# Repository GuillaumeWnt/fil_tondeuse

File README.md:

View this project on [CADLAB.io](https://cadlab.io/project/30614).

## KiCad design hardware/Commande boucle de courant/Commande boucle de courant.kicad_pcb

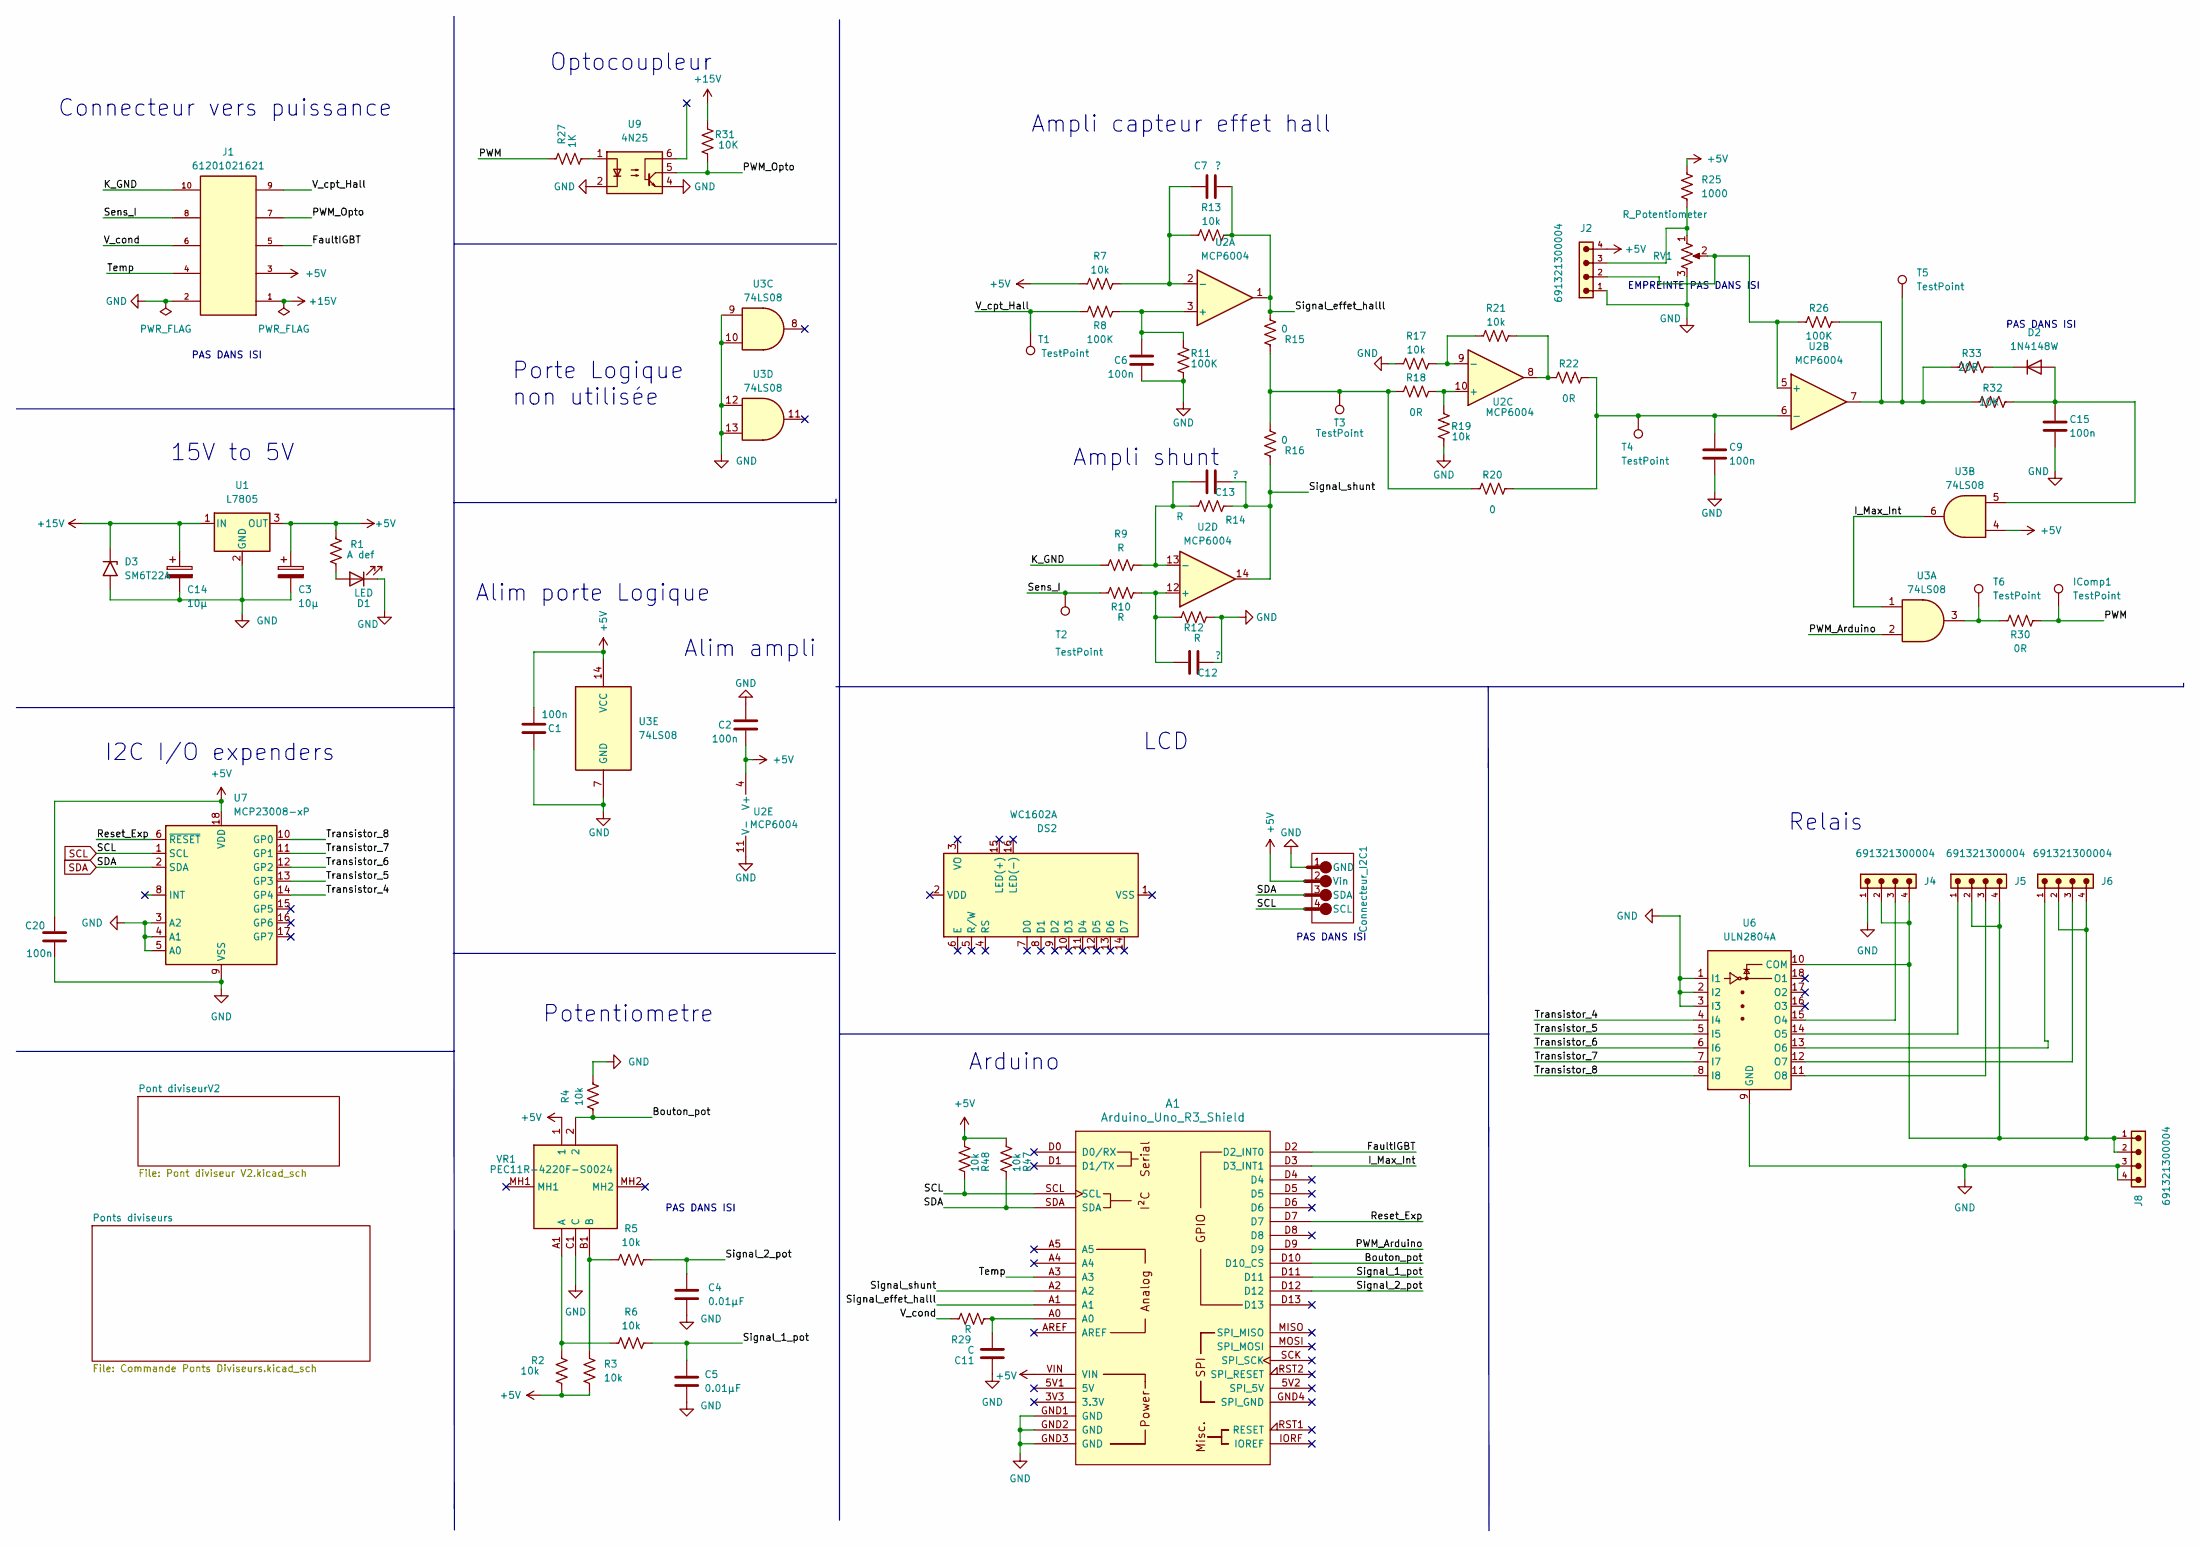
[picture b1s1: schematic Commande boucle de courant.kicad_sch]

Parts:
A1: Arduino_Uno_R3_Shield; Arduino_Uno_R3_Shield_LonPad
C1, C2, C6, C9, C15, C20: 100n; C_0805_2012Metric_Pad1.18x1.45mm_HandSolder
C3, C14: 10µ; C_1206_3216Metric
C4, C5: 0.01µF; C_1206_3216Metric
C7, C12, C13: ?; C_0805_2012Metric_Pad1.18x1.45mm_HandSolder
C11: C; C_1206_3216Metric
Connecteur_I2C1: Connecteur I2C
D1: LED; C_1206_3216Metric
D2: 1N4148W; D_SOD-123
D3: SM6T22A; D_SMB
DS2: WC1602A
IComp1: TestPoint; TestPoint_Keystone_5000-5004_Miniature
J1: 61201021621; Connecteur_10pins
J2, J4, J5, J6, J8: 691321300004; 691321100004; PART-NUMBER 691321100004
R1: A def; R_1206_3216Metric_Pad1.30x1.75mm_HandSolder
R2, R3, R4, R5, R6, R7, R13, R17, R19, R21, R47, R48: 10k; R_1206_3216Metric_Pad1.30x1.75mm_HandSolder
R8, R11, R26: 100K; R_1206_3216Metric_Pad1.30x1.75mm_HandSolder
R9, R10, R12, R14, R29: R; R_1206_3216Metric_Pad1.30x1.75mm_HandSolder
R15, R16, R20: 0; R_1206_3216Metric_Pad1.30x1.75mm_HandSolder
R18, R22, R30: 0R; R_1206_3216Metric_Pad1.30x1.75mm_HandSolder
R25: 1000; R_1206_3216Metric_Pad1.30x1.75mm_HandSolder
R27: 1K; R_1206_3216Metric_Pad1.30x1.75mm_HandSolder
R31, R32: 10K; R_1206_3216Metric_Pad1.30x1.75mm_HandSolder
R33: 20R; R_1206_3216Metric_Pad1.30x1.75mm_HandSolder
RV1: R_Potentiometer; Pot num TRIM_3296W-1-103LF
T1, T2, T3, T4, T5, T6: TestPoint; TestPoint_Keystone_5000-5004_Miniature
U1: L7805; TO-220-3_Vertical_Long
U2: MCP6004; TSSOP-14_4.4x5mm_P0.65mm
U3: 74LS08; SO_SOIC-14_3.9x8.7mm_P1.27mm
U6: ULN2804A; DIP-18_W7.62mm_LongPads
U7: MCP23008-xP; DIP-18_W7.62mm_LongPads
U9: 4N25; DIP-6_W7.62mm_LongPads
VR1: PEC11R-4220F-S0024; Potentiometre; Manufacturer_Part_Number PEC11R-4220F-S0024; Mouser Part Number 652-PEC11R-4220F-S24

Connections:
+5V: A1.VIN, C1.2, C2.2, C3.1, C20.2, Connecteur_I2C1.2 (Vin), J1.3, J2.4, R1.1, R2.2, R3.2, R7.2, R25.2, R47.1, R48.1, U1.3 (OUT), U2.4 (V+), U3.4, U3.14 (VCC), U7.18 (VDD), VR1.1; also elsewhere on the board
+15V: C14.1, D3.1 (A1), J1.1, R31.1, U1.1 (IN)
/Bouton_pot: A1.D10 (D10_CS), R4.2, VR1.2
/FaultIGBT: A1.D2 (D2_INT0), J1.5
/I_Max_Int: A1.D3 (D3_INT1), U3.1, U3.6
/K_GND: J1.10, R9.1
/PWM: IComp1.1, R27.1, R30.1
/PWM_Arduino: A1.D9, U3.2
/PWM_Opto: J1.7, R31.2, U9.5
/Reset_Exp: A1.D7, U7.6 (~RESET)
/Sens_I: J1.8, R10.1, T2.1
/Signal_1_pot: A1.D11, C5.1, R6.2
/Signal_2_pot: A1.D12, C4.2, R5.1
/Signal_effet_halll: A1.A1, C7.2, R13.1, R15.1, U2.1
/Signal_shunt: A1.A2, C13.2, R14.2, R16.2, U2.14
/Temp: A1.A3, J1.4
/Transistor_4: U6.4 (I4), U7.14 (GP4)
/Transistor_5: U6.5 (I5), U7.13 (GP3)
/Transistor_6: U6.6 (I6), U7.12 (GP2)
/Transistor_7: U6.7 (I7), U7.11 (GP1)
/Transistor_8: U6.8 (I8), U7.10 (GP0)
/V_cond: J1.6, R29.2
/V_cpt_Hall: J1.9, R8.2, T1.1
GND: A1.GND1 (GND), A1.GND2 (GND), A1.GND3 (GND), C1.1, C2.1, C3.2, C4.1, C5.2, C6.2, C9.2, C11.1, C12.2, C14.2, C15.2, C20.1, Connecteur_I2C1.1 (GND), D1.1 (K), D3.2 (A2), J1.2, J2.1, J4.1, J8.3, J8.4, R4.1, R11.2, R12.2, R17.2, R19.2, RV1.3, U1.2 (GND), U2.11 (V-), U3.7 (GND), U3.9, U3.10, U3.12, U3.13, U6.1 (I1), U6.2 (I2), U6.3 (I3), U6.9 (GND), U7.3 (A2), U7.4 (A1), U7.5 (A0), U7.9 (VSS), U9.2, U9.4, VR1.C1 (C); also elsewhere on the board
unnamed: A1.A0, C11.2, R29.1
unnamed: D1.2 (A), R1.2
unnamed: C15.1, D2.2 (A), R32.2, U3.5
unnamed: D2.1 (K), R33.2
unnamed: J2.3, R25.1, RV1.1
unnamed: R15.2, R16.1, R18.1, R20.1, T3.1
unnamed: R21.1, R22.1, U2.8
unnamed: R26.2, R32.1, R33.1, T5.1, U2.7
unnamed: R27.2, U9.1
unnamed: R30.2, T6.1, U3.3
unnamed: C6.1, R8.1, R11.1, U2.3 (+)
unnamed: C7.1, R7.1, R13.2, U2.2 (-)
unnamed: J2.2, R26.1, RV1.2, U2.5 (+)
unnamed: C9.1, R20.2, R22.2, T4.1, U2.6 (-)
unnamed: R18.2, R19.1, U2.10 (+)
unnamed: R17.1, R21.2, U2.9 (-)
unnamed: C12.1, R10.2, R12.1, U2.12 (+)
unnamed: C13.1, R9.2, R14.1, U2.13 (-)
unnamed: J4.2, J4.4, J5.2, J5.4, J6.2, J6.4, J8.1, J8.2, U6.10 (COM)
unnamed: J4.3, U6.15 (O4)
unnamed: J5.1, U6.14 (O5)
unnamed: J6.1, U6.13 (O6)
unnamed: J6.3, U6.12 (O7)
unnamed: J5.3, U6.11 (O8)
unnamed: R2.1, R6.1, VR1.A1 (A)
unnamed: R3.1, R5.2, VR1.B1 (B)
SCL: A1.SCL, Connecteur_I2C1.4 (SCL), R48.2, U7.1 (SCL); also elsewhere on the board
SDA: A1.SDA, Connecteur_I2C1.3 (SDA), R47.2, U7.2 (SDA); also elsewhere on the board

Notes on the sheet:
Relais
Porte Logique non utilisée
PAS DANS ISI
Ampli capteur effet hall
Optocoupleur
15V to 5V
I2C I/O expenders
Ampli shunt
Potentiometre
Alim ampli
EMPREINTE PAS DANS ISI
Connecteur vers puissance
LCD
Alim porte Logique
Arduino

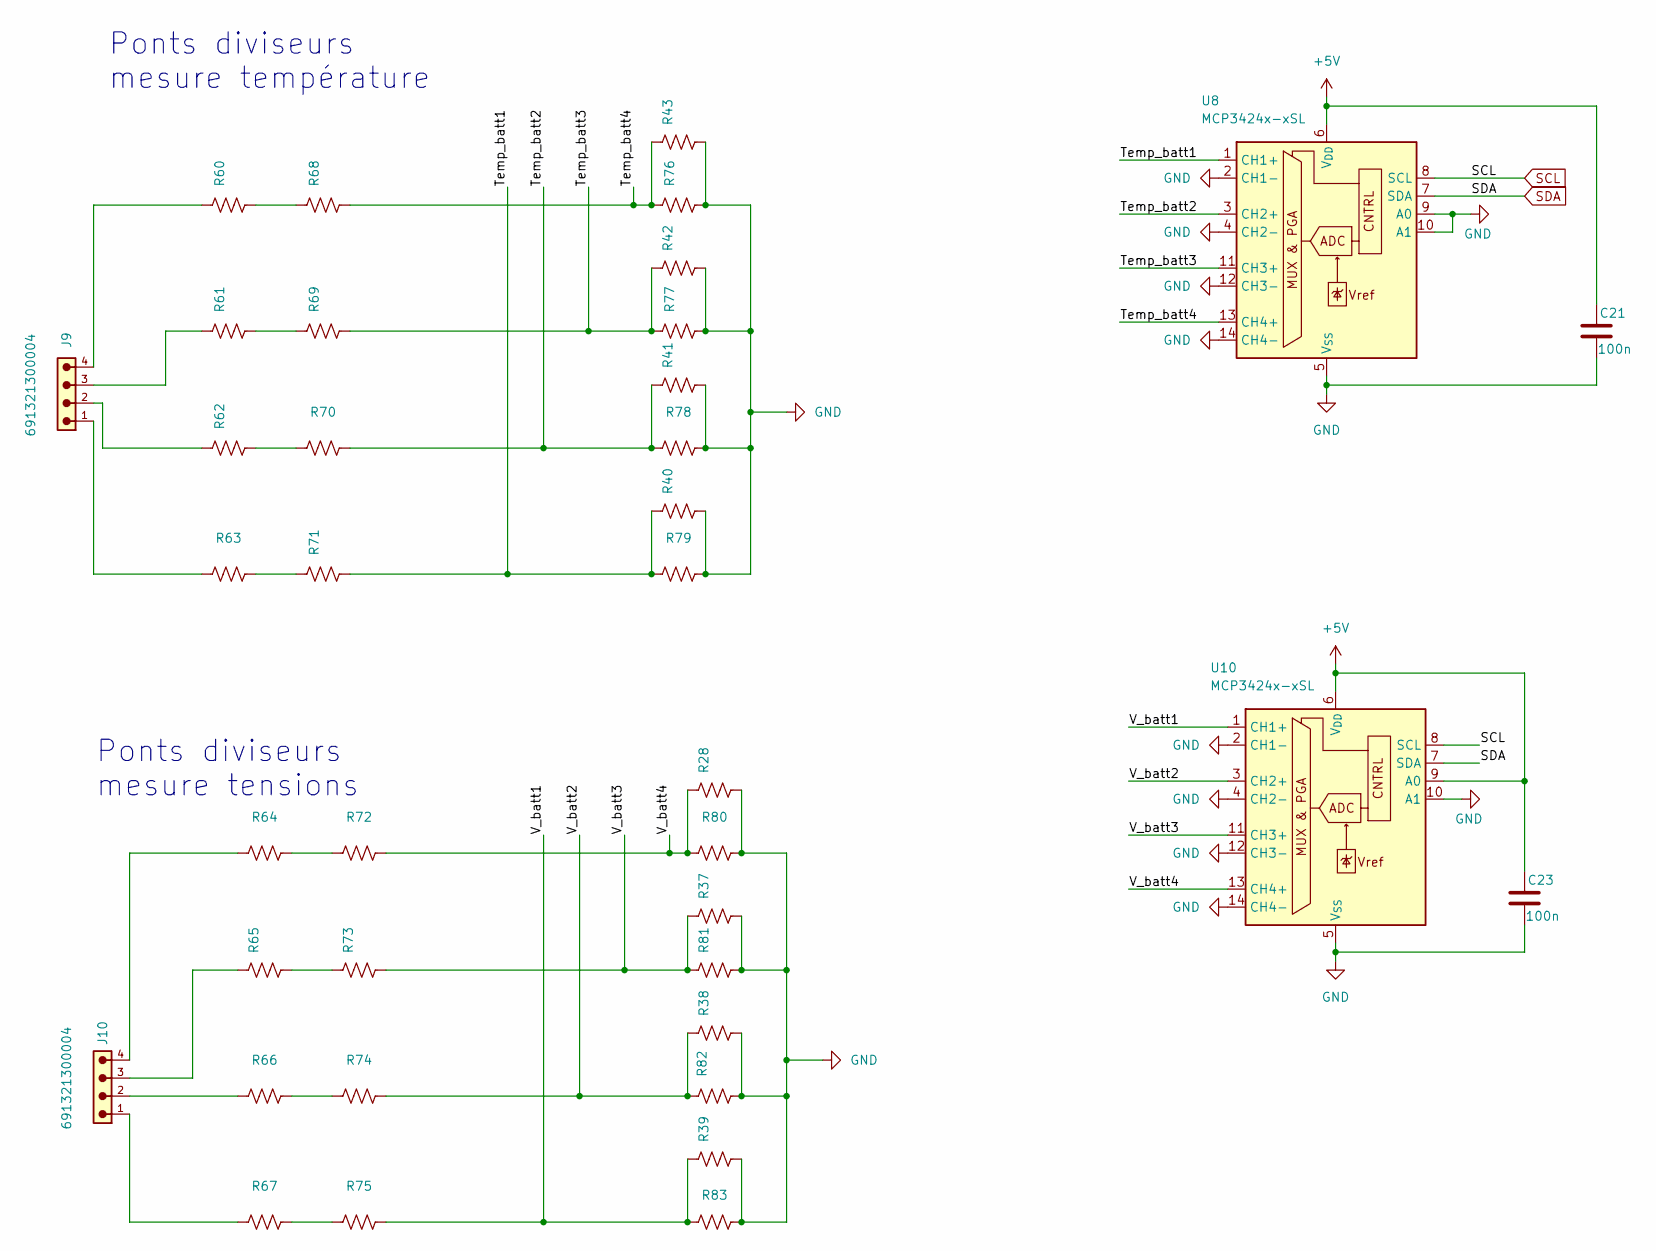
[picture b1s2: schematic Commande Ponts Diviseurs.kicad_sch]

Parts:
C21, C23: 100n; C_1206_3216Metric_Pad1.33x1.80mm_HandSolder
J9, J10: 691321300004; Connecteur_4pins; PART-NUMBER 691321300004
R28, R37, R38, R39, R40, R41, R42, R43, R60, R61, R62, R63, R64, R65, R66, R67, R68, R69, R70, R71, R72, R73, R74, R75, R76, R77, R78, R79, R80, R81, R82, R83: R_1206_3216Metric_Pad1.30x1.75mm_HandSolder
U8, U10: MCP3424x-xSL; SO_SOIC-14_3.9x8.7mm_P1.27mm

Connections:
+5V: C21.1, C23.1, U8.6 (V_{DD}), U10.6 (V_{DD}), U10.9 (A0); also elsewhere on the board
/Ponts diviseurs/Temp_batt1: R40.1, R71.2, R79.1, U8.1 (CH1+)
/Ponts diviseurs/Temp_batt2: R41.1, R70.2, R78.1, U8.3 (CH2+)
/Ponts diviseurs/Temp_batt3: R42.1, R69.2, R77.1, U8.11 (CH3+)
/Ponts diviseurs/Temp_batt4: R43.1, R68.2, R76.1, U8.13 (CH4+)
/Ponts diviseurs/V_batt1: R39.1, R75.2, R83.1, U10.1 (CH1+)
/Ponts diviseurs/V_batt2: R38.1, R74.2, R82.1, U10.3 (CH2+)
/Ponts diviseurs/V_batt3: R37.1, R73.2, R81.1, U10.11 (CH3+)
/Ponts diviseurs/V_batt4: R28.1, R72.2, R80.1, U10.13 (CH4+)
GND: C21.2, C23.2, R28.2, R37.2, R38.2, R39.2, R40.2, R41.2, R42.2, R43.2, R76.2, R77.2, R78.2, R79.2, R80.2, R81.2, R82.2, R83.2, U8.2 (CH1-), U8.4 (CH2-), U8.5 (V_{SS}), U8.9 (A0), U8.10 (A1), U8.12 (CH3-), U8.14 (CH4-), U10.2 (CH1-), U10.4 (CH2-), U10.5 (V_{SS}), U10.10 (A1), U10.12 (CH3-), U10.14 (CH4-); also elsewhere on the board
unnamed: J9.1, R63.1
unnamed: J9.2, R62.1
unnamed: J9.3, R61.1
unnamed: J9.4, R60.1
unnamed: J10.1, R67.1
unnamed: J10.2, R66.1
unnamed: J10.3, R65.1
unnamed: J10.4, R64.1
unnamed: R60.2, R68.1
unnamed: R61.2, R69.1
unnamed: R62.2, R70.1
unnamed: R63.2, R71.1
unnamed: R64.2, R72.1
unnamed: R65.2, R73.1
unnamed: R66.2, R74.1
unnamed: R67.2, R75.1
SCL: U8.8 (SCL), U10.8 (SCL); also elsewhere on the board
SDA: U8.7 (SDA), U10.7 (SDA); also elsewhere on the board

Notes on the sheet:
Ponts diviseurs mesure température
Ponts diviseurs mesure tensions

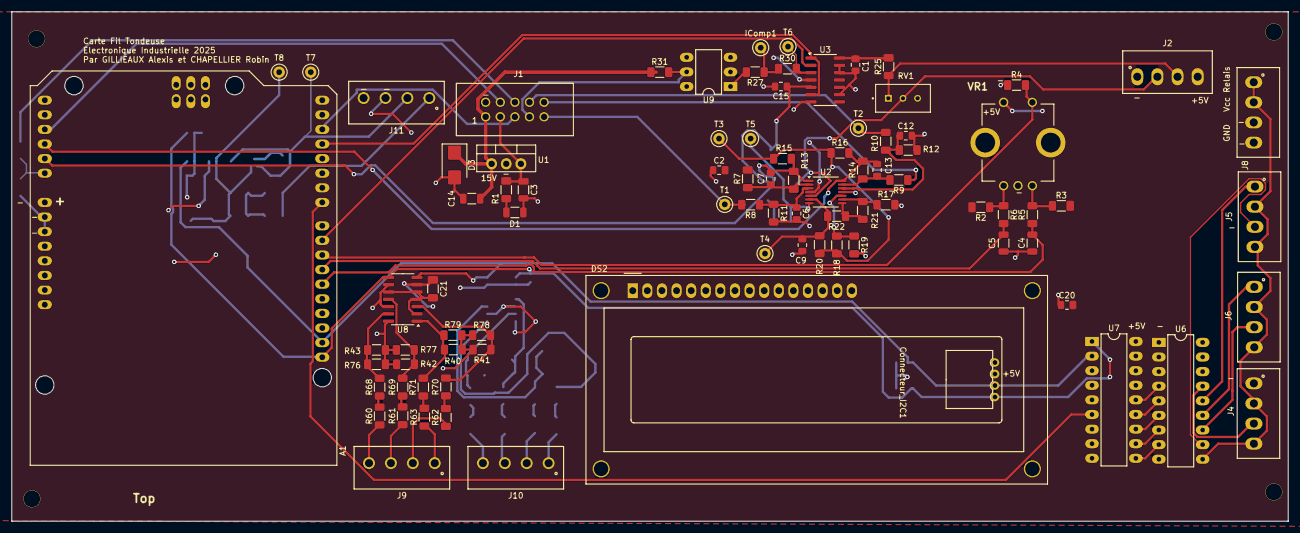
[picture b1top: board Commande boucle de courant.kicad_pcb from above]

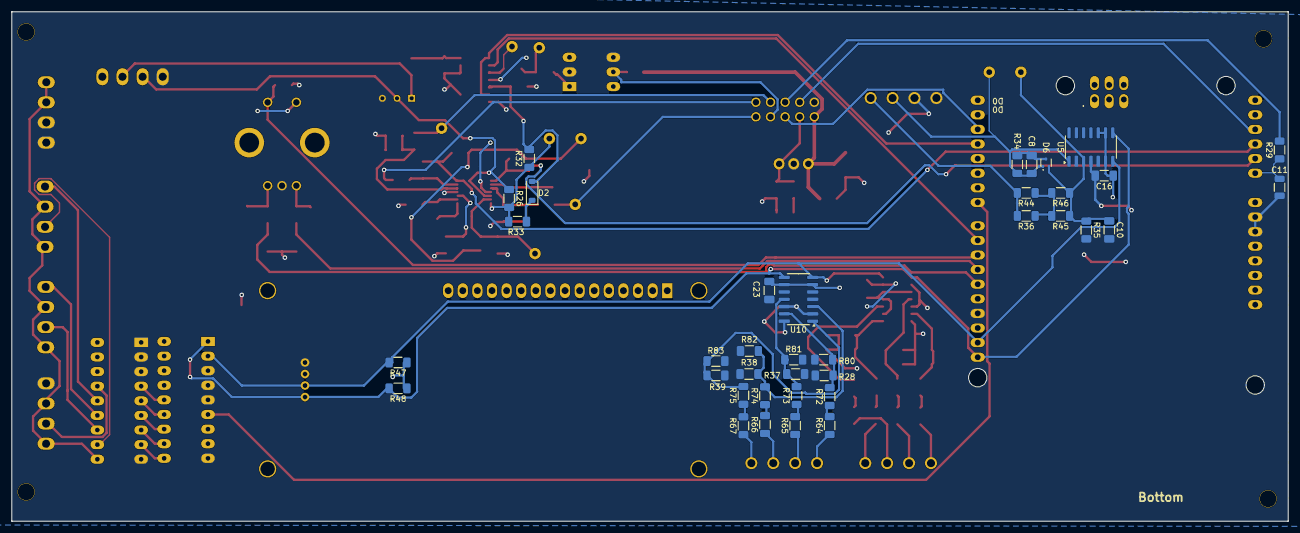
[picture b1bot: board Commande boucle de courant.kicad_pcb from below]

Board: 2 copper layers, 222.0 x 88.6 mm, 129 parts (38 on the bottom side), 80 nets.

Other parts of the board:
C8, C10: 10µ; C_1206_3216Metric_Pad1.33x1.80mm_HandSolder
C16: 100n; C_1206_3216Metric_Pad1.33x1.80mm_HandSolder
D6: RCLAMP0582BQTCT; SOT-523
H1, H2, H3, H4: MountingHole_Pad; MountingHole_3mm
J11: 691321100004; Connecteur_4pins
R34: 243; R_1206_3216Metric_Pad1.30x1.75mm_HandSolder
R35, R45, R46: 1K; R_1206_3216Metric_Pad1.30x1.75mm_HandSolder
R36, R44: 27K; R_1206_3216Metric_Pad1.30x1.75mm_HandSolder
T7, T8: TestPoint; TestPoint_Keystone_5000-5004_Miniature
U5: MCP3424x-xSL; SO_SOIC-14_3.9x8.7mm_P1.27mm

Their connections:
+5V: C16.1, U5.6 (V_{DD}), U5.9 (A0), U5.10 (A1); also elsewhere on the board
/Pont diviseurV2/Temp_batt1: C8.1, D6.1 (K1), J11.2, R34.1, T7.1, U5.1 (CH1+)
/Pont diviseurV2/Tension_batt1: C10.1, D6.2 (K2), R35.1, R45.1, R46.1, T8.1, U5.3 (CH2+)
GND: C8.2, C10.2, C16.2, D6.3 (A), J11.3, J11.4, R34.2, R35.2, U5.2 (CH1-), U5.4 (CH2-), U5.5 (V_{SS}); also elsewhere on the board
unnamed: J11.1, R36.2, R44.2
unnamed: R36.1, R44.1, R45.2, R46.2
SCL: U5.8 (SCL); also elsewhere on the board
SDA: U5.7 (SDA); also elsewhere on the board

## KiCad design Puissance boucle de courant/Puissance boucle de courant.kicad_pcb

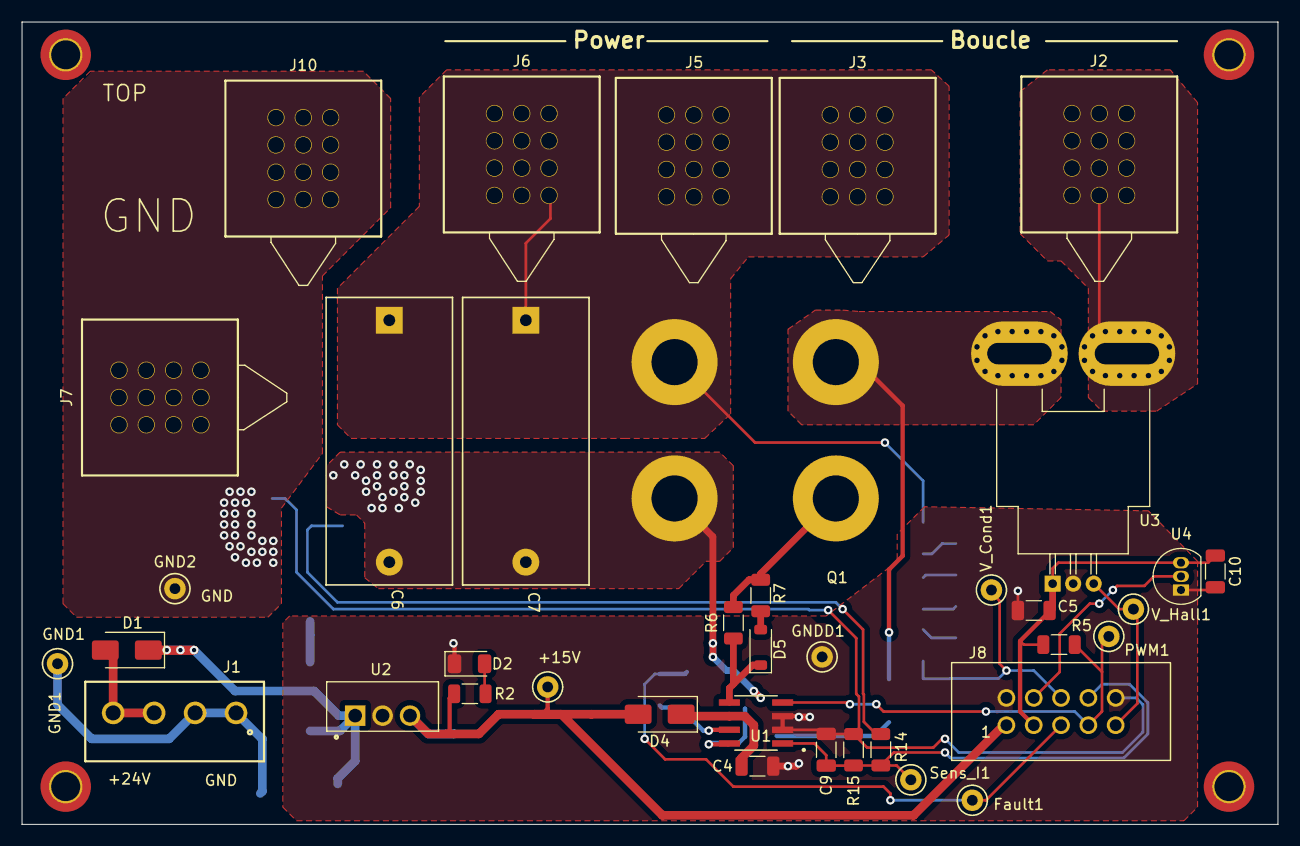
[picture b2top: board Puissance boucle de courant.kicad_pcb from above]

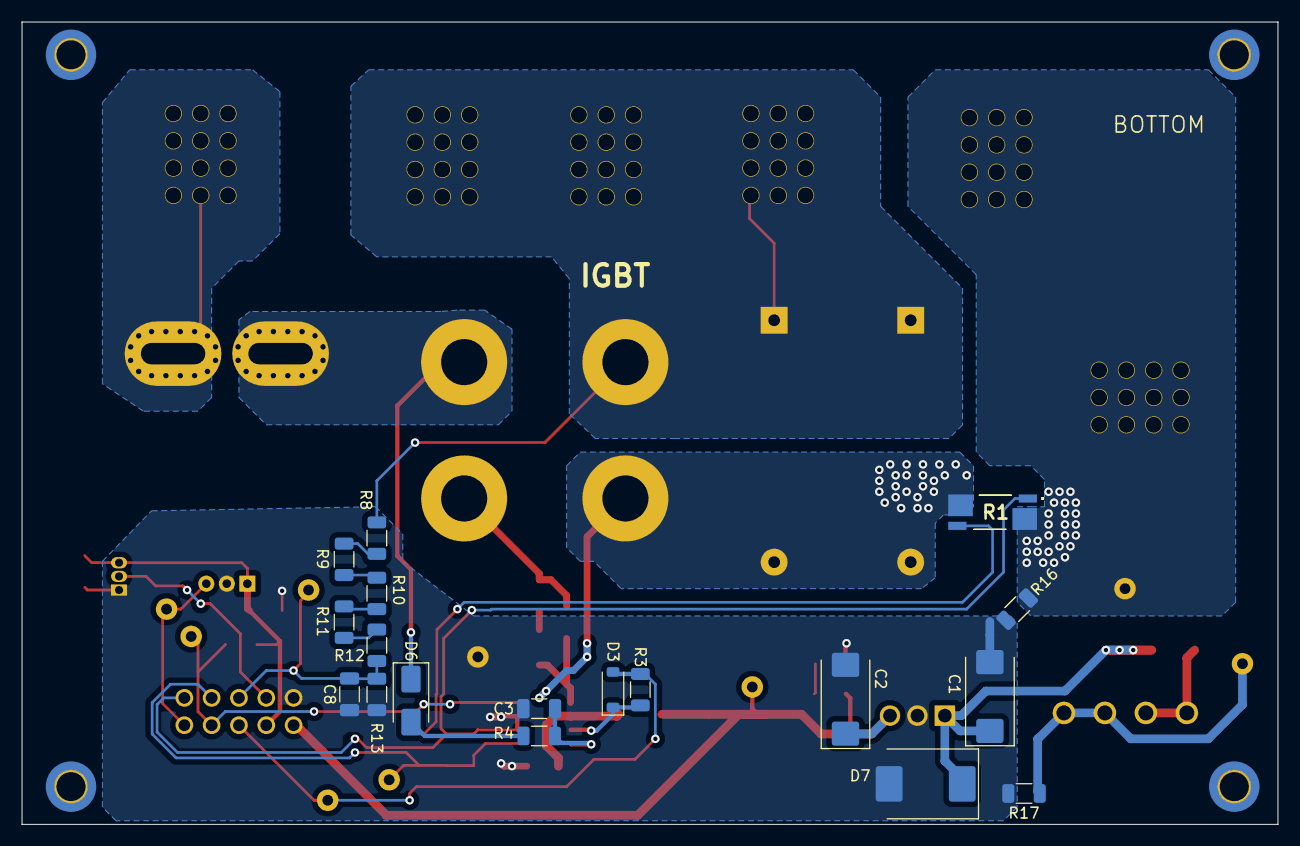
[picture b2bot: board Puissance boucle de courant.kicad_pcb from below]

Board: 2 copper layers, 116.8 x 74.6 mm, 60 parts (18 on the bottom side), 30 nets.

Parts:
C1, C2: 10µF; CP_EIA-7343-30_AVX-N_Pad2.25x2.55mm_HandSolder
C3, C4: 10µF; C_1206_3216Metric
C5, C8, C9, C10: 100nF; C_1206_3216Metric
C6, C7: 1µF; CAP_890334026027_WRE
D1, D4, D6: NRVA4007T3G; D_SMA
D2: LED; LED_1206_3216Metric
D3, D5: D_SOD-123
D7: B320; D_SMC
Fault1: TestPoint; TestPoint_Keystone_5000-5004_Miniature
GND1, GND2: TestPoint; TestPoint_Keystone_5000-5004_Miniature
GNDD1: TestPoint; TestPoint_Keystone_5000-5004_Miniature
H1, H2, H3, H4: MountingHole; MountingHole_2.7mm_M2.5_DIN965_Pad_TopBottom
J1: 691321300004
J2, J3, J5, J6, J7, J10: Conn_01x01_Socket; WP-PLUG_7464000
J8: 61201021621
PWM1: TestPoint; TestPoint_Keystone_5000-5004_Miniature
Q1: APT75GT120JU2; GENESIC_MBR200100CTS bis
R1: 0,002R; WSK25122L000FEA
R2, R3, R4, R6, R7, R14, R15: R; R_1206_3216Metric
R5, R13: 5k; R_1206_3216Metric
R8, R9, R10, R11: 50k; R_1206_3216Metric
R12: 11k; R_1206_3216Metric
R16, R17: 0R; R_1206_3216Metric
Sens_I1: TestPoint; TestPoint_Keystone_5000-5004_Miniature
TP3: TestPoint; TestPoint_Keystone_5000-5004_Miniature
U1: MC33153DG; SOIC127P600X265-8N
U2: L7815; TO255P1040X460X1935-3
U3: ACS770xCB-050U-PFF; Allegro_CB_PFF
U4: DS18B20; TO-92_Inline
V_Cond1: TestPoint; TestPoint_Keystone_5000-5004_Miniature
V_Hall1: TestPoint; TestPoint_Keystone_5000-5004_Miniature

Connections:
+5V: C5.1, C10.1, J8.3, R5.1, U3.1 (VCC), U4.3 (V_{DD})
+15V: C2.1, D4.2 (A), J8.1, R2.1, TP3.1, U2.3 (OUT)
+24V: C1.1, D1.1 (K), D7.1 (K), U2.1 (IN)
/+Boucle: C6.1, C7.1, J3.1, J5.1, J6.1, Q1.3 (K), R8.1
/-Boucle: J2.1, U3.4 (IP+)
/Driver_out: D5.1 (K), R6.1, U1.5 (DRIVE_OUT)
/FaultIGBT: D3.2 (A), Fault1.1, J8.5, R3.1
/PWM_Arduino: J8.7, PWM1.1, R5.2, U1.4 (~INPUT)
/Sens_I: C9.1, J8.8, R14.2, R15.1, Sens_I1.1, U1.1 (CURRENT_SEN_IN)
/Temp: J8.4, U4.2 (DQ)
/V_cond: C8.2, J8.6, R12.2, R13.1, V_Cond1.1
/V_cpt_Hall: J8.9, U3.3 (VIOUT), V_Hall1.1
/Vout_IGBT: C6.2, C7.2, Q1.1 (E), R1.I2
/Vout_cpt: D6.1 (K), Q1.4 (C), U3.5 (IP-)
GND: GND2.1, J7.1, J10.1, R1.I1, R16.2
GND1: GND1.1, J1.1, J1.2, R17.1
GNDD: C1.2, C2.2, C3.2, C4.2, C5.2, C8.1, C9.2, C10.2, D2.1 (K), D7.2 (A), GNDD1.1, J8.2, J8.10, R1.E1, R13.2, R15.2, R16.1, R17.2, U1.2 (KELVIN_GND), U1.3 (VEE), U2.2 (GND), U3.2 (GND), U4.1 (GND)
unnamed: D1.2 (A), J1.3, J1.4
unnamed: D2.2 (A), R2.2
unnamed: D3.1 (K), R3.2, U1.7 (FAULT_OUT)
unnamed: C4.1, D4.1 (K), U1.6 (VCC)
unnamed: D5.2 (A), R7.1
unnamed: D6.2 (A), R4.1
unnamed: Q1.2 (G), R6.2, R7.2
unnamed: R1.E2, R14.1
unnamed: R8.2, R9.1
unnamed: R9.2, R10.1
unnamed: R10.2, R11.1
unnamed: R11.2, R12.1
unnamed: C3.1, R4.2, U1.8 (FAULT_BLANKING/DESATURATION_IN)
